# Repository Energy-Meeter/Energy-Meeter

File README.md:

# Energy Meeter

An esp32-powered smart plug and online dashboard.

## Features

- Online dashboard
- WiFi communication
- Capable of analyzing the power consumption of an arbitrary load
- 5A current rating

## Hardware

### Board Revision A

Status: Testing

The current revision of the energy meeter. We just received it from PCBWay, and we're now in the process of assembling and validating it.

#### Schematic

#### Board

#### Stack Up

## Software

### Networking and Dashboard

### Energy Monitor Library

- [HLW8032 energy monitor library](https://github.com/Energy-Meeter/HLW8032)

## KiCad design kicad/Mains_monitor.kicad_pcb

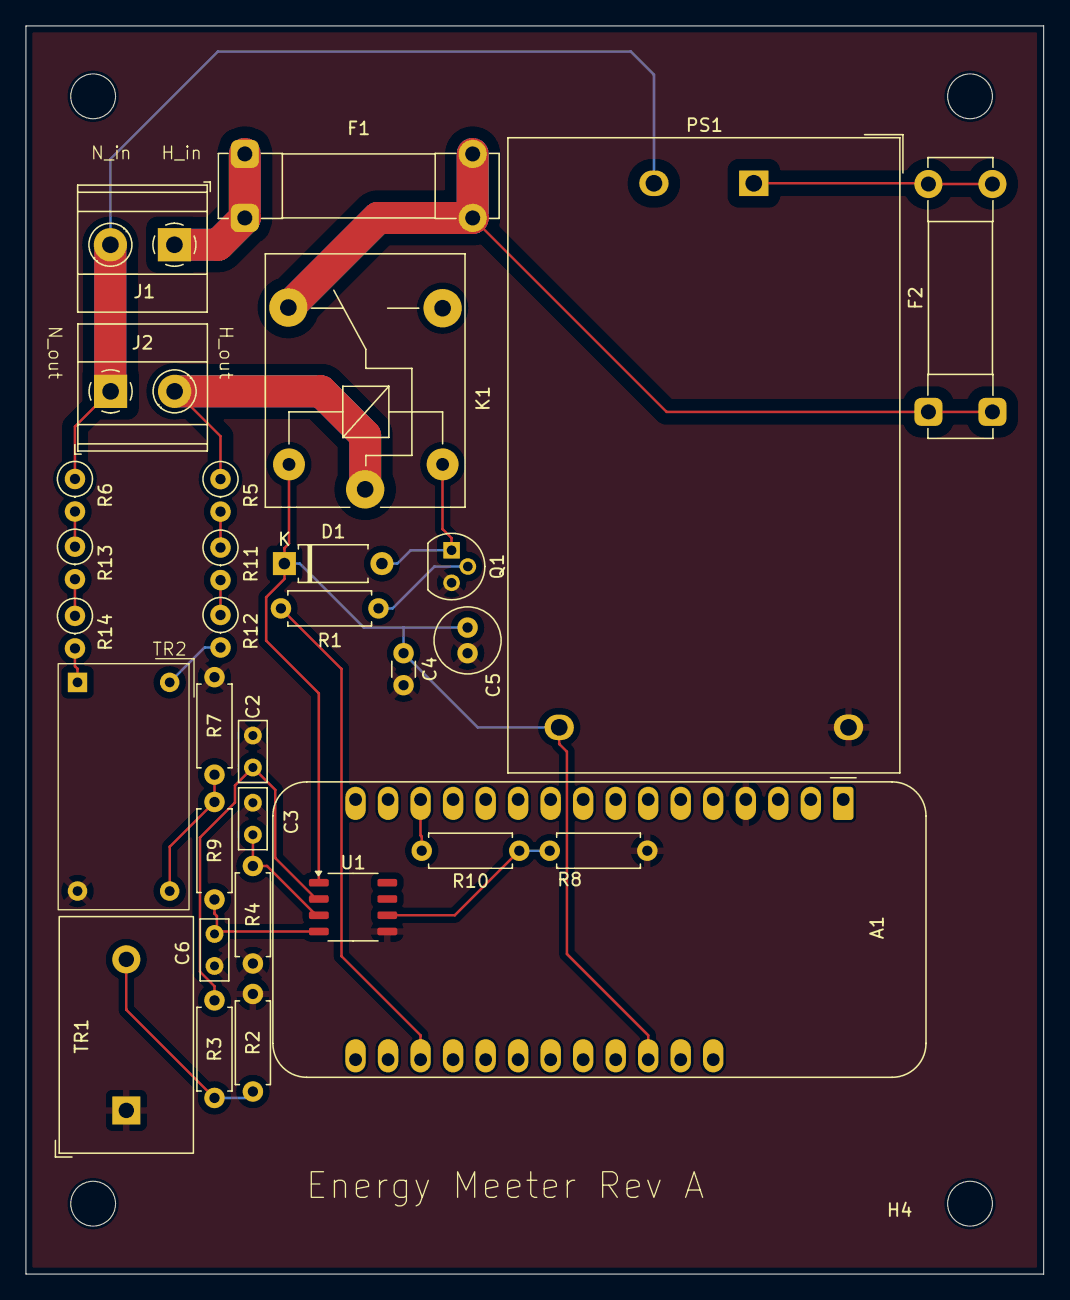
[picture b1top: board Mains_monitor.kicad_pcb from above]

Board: 2 copper layers, 79.5 x 97.5 mm, 35 parts (0 on the bottom side), 23 nets.

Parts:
A1: Adafruit_Feather_HUZZAH32_ESP32; Adafruit_Feather
C2, C3, C6: 33n; C_Rect_L4.6mm_W2.0mm_P2.50mm_MKS02_FKP02
C4: 100n; C_Disc_D3.0mm_W1.6mm_P2.50mm
C5: 10u; C_Radial_D5.0mm_H11.0mm_P2.00mm
D1: D; D_A-405_P7.62mm_Horizontal
F1: 1Ax250V; Fuseholder_Clip-5x20mm_Bel_FC-203-22_Lateral_P17.80x5.00mm_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
F2: 100mAx250V; Fuseholder_Clip-5x20mm_Bel_FC-203-22_Lateral_P17.80x5.00mm_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
H1, H2, H3, H4: MountingHole; MountingHole_3.5mm
J1, J2: Screw_Terminal_01x02; TerminalBlock_Phoenix_MKDS-1,5-2_1x02_P5.00mm_Horizontal
K1: SANYOU_SRD_Form_C; Relay_SPDT_SANYOU_SRD_Series_Form_C
PS1: HLK-10M05; Converter_ACDC_Hi-Link_HLK-10Mxx
Q1: Q_NPN_CBE; TO-92
R1: TBD; R_Axial_DIN0207_L6.3mm_D2.5mm_P7.62mm_Horizontal
R2: 49.9 (1%); R_Axial_DIN0207_L6.3mm_D2.5mm_P7.62mm_Horizontal
R3, R4, R9: 1k; R_Axial_DIN0207_L6.3mm_D2.5mm_P7.62mm_Horizontal
R5, R6, R11, R12, R13, R14: 10K; R_Axial_DIN0207_L6.3mm_D2.5mm_P2.54mm_Vertical
R7: 75 (1%); R_Axial_DIN0207_L6.3mm_D2.5mm_P7.62mm_Horizontal
R8: 5k1; R_Axial_DIN0207_L6.3mm_D2.5mm_P7.62mm_Horizontal
R10: 10k; R_Axial_DIN0207_L6.3mm_D2.5mm_P7.62mm_Horizontal
TR1: ZMCT103C; Transformer_Zeming_ZMCT103C
TR2: ZMPT107; ZMPT107-1
U1: HLW8032; SSOP-8_3.9x5.05mm_P1.27mm

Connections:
+5V: A1.26 (USB), C4.1, C5.2, D1.1 (K), K1.5, PS1.4 (+Vout), U1.1 (VDD)
/DATA_HV: R8.1, R10.1, U1.6 (TX)
/DATA_LV: A1.14 (RX/IO16), R10.2
/RLY_CTRL: A1.19 (A6/IO14), R1.1
AC_H: F1.2, F2.1, K1.4
AC_N: J1.2, J2.1, PS1.2 (AC/N), R6.1
GND: A1.4 (GND), C2.2, C3.1, C4.2, C5.1, C6.2, PS1.3 (-Vout), Q1.3 (E), R2.2, R4.1, R7.1, R8.2, TR1.1, TR2.3, U1.5 (GND)
IN: C3.2, R4.2, U1.3 (IN)
IP: C2.1, R3.2, U1.2 (IP)
unnamed: D1.2 (A), K1.2, Q1.1 (C)
unnamed: F1.1, J1.1
unnamed: F2.2, PS1.1 (AC/L)
unnamed: Q1.2 (B), R1.2
unnamed: R2.1, R3.1, TR1.2
unnamed: R7.2, R9.1, TR2.4
unnamed: R5.2, R11.1
unnamed: R11.2, R12.1
unnamed: R12.2, TR2.2
unnamed: R6.2, R13.1
unnamed: R13.2, R14.1
unnamed: R14.2, TR2.1
RELAY_OUT: J2.2, K1.1, R5.1
VP: C6.1, R9.2, U1.4 (VP)

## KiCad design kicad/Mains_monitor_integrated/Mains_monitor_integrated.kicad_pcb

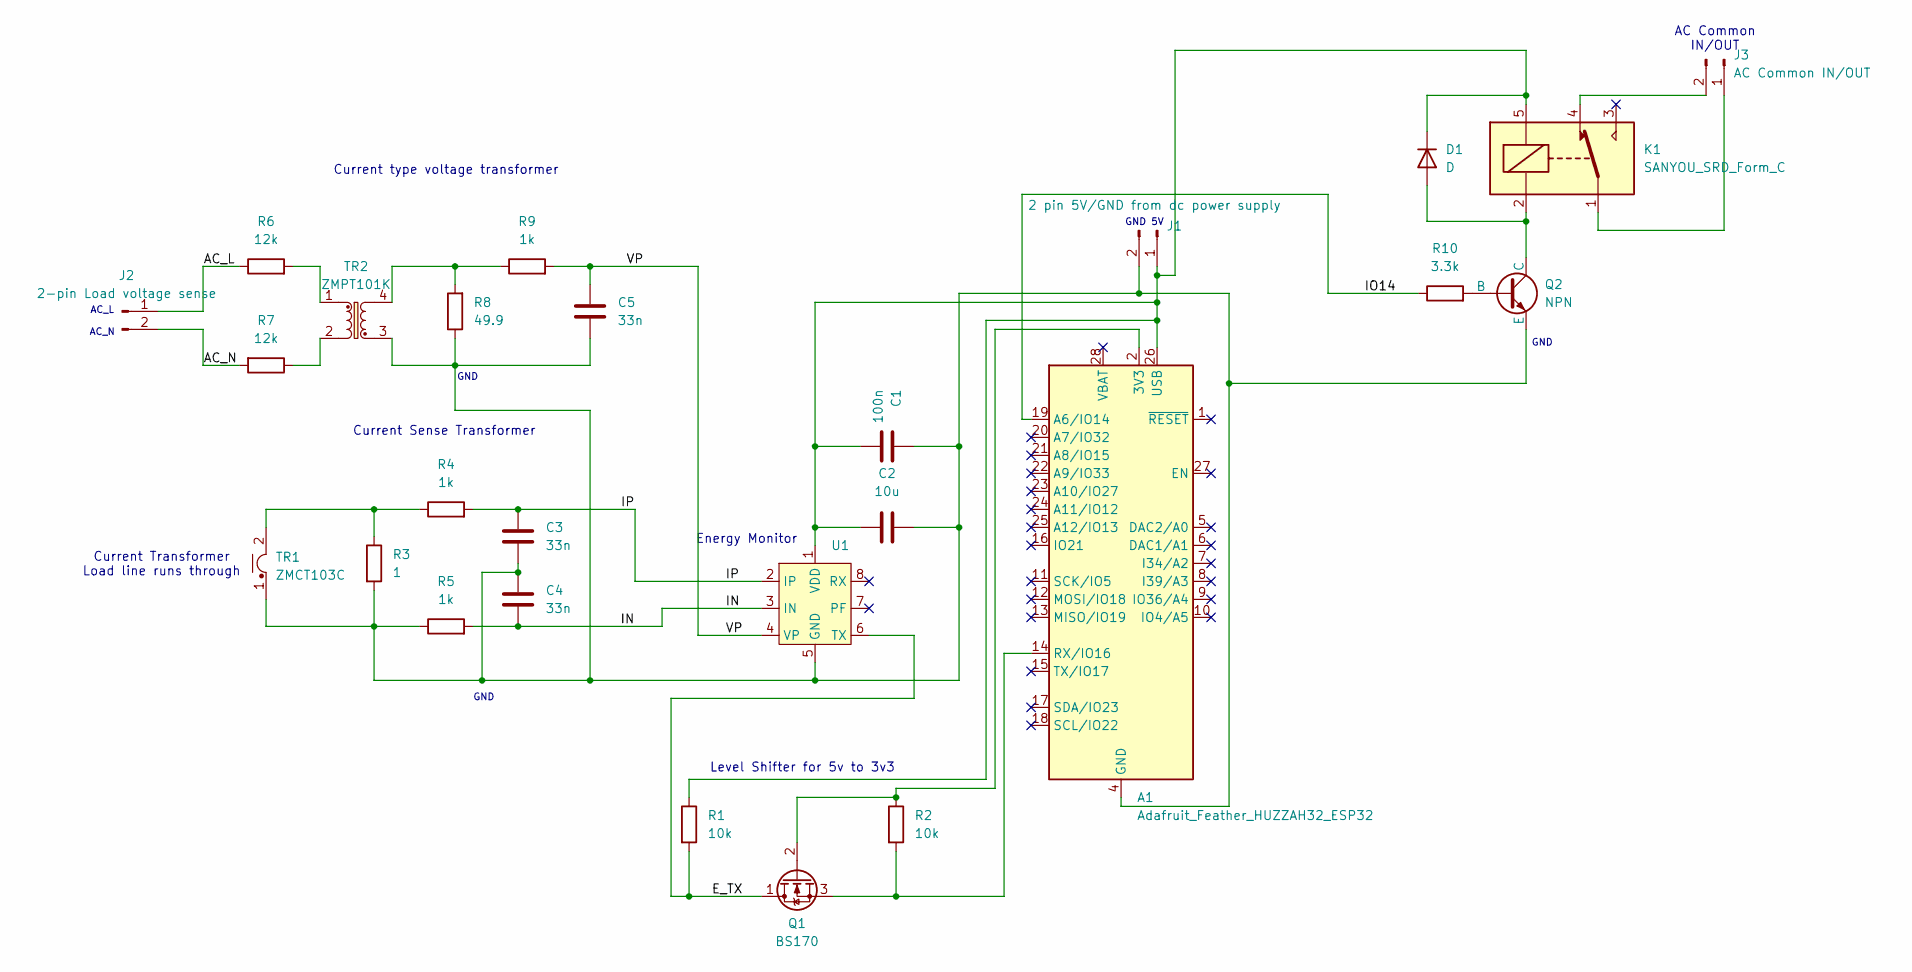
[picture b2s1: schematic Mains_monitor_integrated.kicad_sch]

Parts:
A1: Adafruit_Feather_HUZZAH32_ESP32; Adafruit_Feather
C1: 100n; C_0805_2012Metric_Pad1.18x1.45mm_HandSolder
C2: 10u; C_0805_2012Metric_Pad1.18x1.45mm_HandSolder
C3, C4, C5: 33n; C_0805_2012Metric_Pad1.18x1.45mm_HandSolder
D1: D; D_5W_P10.16mm_Horizontal
J1: 2 pin 5V/GND from dc power supply; PinSocket_1x02_P2.54mm_Vertical
J2: 2-pin Load voltage sense; PinHeader_1x02_P2.54mm_Vertical
J3: AC Common IN/OUT; PinHeader_1x02_P2.54mm_Vertical
K1: SANYOU_SRD_Form_C; Relay_SPDT_SANYOU_SRD_Series_Form_C
Q1: BS170; TO-92_Inline
Q2: NPN; TO-92_Inline
R1, R2: 10k; R_Axial_DIN0414_L11.9mm_D4.5mm_P5.08mm_Vertical
R3: 1; R_Axial_DIN0414_L11.9mm_D4.5mm_P5.08mm_Vertical
R4, R5, R9: 1k; R_Axial_DIN0414_L11.9mm_D4.5mm_P5.08mm_Vertical
R6, R7: 12k; R_Axial_DIN0414_L11.9mm_D4.5mm_P5.08mm_Vertical
R8: 49.9; R_Axial_DIN0414_L11.9mm_D4.5mm_P5.08mm_Vertical
R10: 3.3k; R_Axial_DIN0414_L11.9mm_D4.5mm_P5.08mm_Vertical
TR1: ZMCT103C; Transformer_Zeming_ZMCT103C
TR2: ZMPT101K; Transformer_Zeming_ZMPT101K
U1: HLW8032; SSOP-8_3.9x5.05mm_P1.27mm

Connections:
/AC_L: J2.1, R6.1
/AC_N: J2.2, R7.2
/E_TX: Q1.1 (D), R1.2, U1.6 (TX)
/IN: C4.2, R5.2, U1.3 (IN)
/IO14: A1.19 (A6/IO14), R10.1
/IP: C3.1, R4.2, U1.2 (IP)
/VP: C5.1, R9.2, U1.4 (VP)
unnamed: A1.2 (3V3), Q1.2 (G), R2.1
unnamed: A1.4 (GND), C1.1, C2.1, C3.2, C4.1, C5.2, J1.2, Q2.3 (E), R3.2, R5.1, R8.1, TR1.1, TR2.3, U1.5 (GND)
unnamed: A1.14 (RX/IO16), Q1.3 (S), R2.2
unnamed: A1.26 (USB), C1.2, C2.2, D1.1 (K), J1.1, K1.5, R1.1, U1.1 (VDD)
unnamed: D1.2 (A), K1.2, Q2.1 (C)
unnamed: J3.1, K1.1
unnamed: J3.2, K1.4
unnamed: Q2.2 (B), R10.2
unnamed: R3.1, R4.1, TR1.2
unnamed: R6.2, TR2.1
unnamed: R7.1, TR2.2
unnamed: R8.2, R9.1, TR2.4

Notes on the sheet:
GND
AC_L AC_N
Level Shifter for 5v to 3v3
AC Common IN/OUT
Current Sense Transformer
GND 5V
Current type voltage transformer
Energy Monitor
Current Transformer Load line runs through

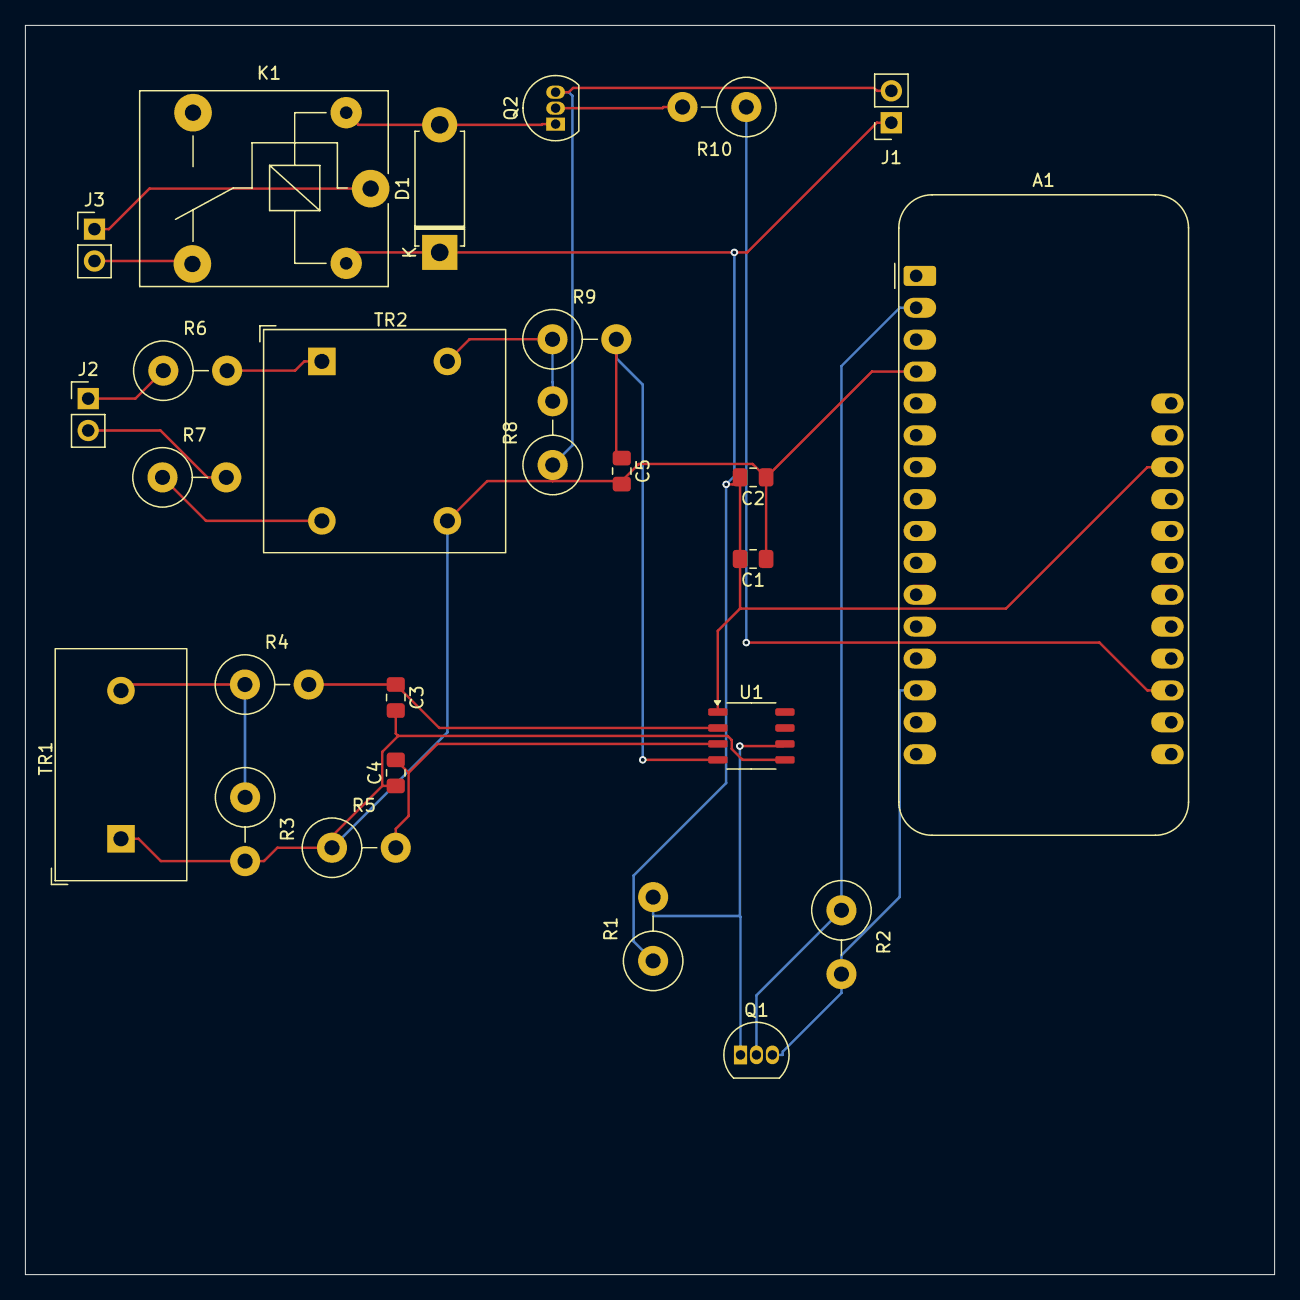
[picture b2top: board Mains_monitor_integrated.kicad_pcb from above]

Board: 2 copper layers, 99.5 x 99.5 mm, 26 parts (0 on the bottom side), 19 nets.

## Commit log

2025-01-01 Init commit
2025-01-01 Create LICENSE
2025-01-01 Design power supply circuit
2025-01-01 Add To Do list
2025-01-17 Add rev0 schematic
2025-01-17 Add pdf of rev0 schematic
2025-01-19 Add git ignore for KiCad Projectt
2025-01-19 Consolidate schematic to a single sheet
2025-01-24 created new schematic to integrate all components into a fully connected final version
2025-01-24 completed rough schematic and built first prototype pcb
2025-01-29 Hello World
2025-01-31 Improve sch clarity
2025-02-03 added footprints for all components, started PCB layout
2025-02-03 added mounting holes and ground layers
2025-02-04 PCB layout updated, traces and base fill added, still need to make space for mounting holes
2025-02-05 added net class for 120V and mounting holes
2025-02-05 backup files
2025-02-06 Update footprints and git ignore
2025-02-06 Get footprint from main
2025-02-06 Added in the correct footprints
2025-02-06 Updated PCB layout with new components, decreased board size
2025-02-06 added updated screw terminal footprints
2025-02-07 Clear ERC, and change Q1
2025-02-07 Clear DRC
2025-02-07 Plot gerbers/drill
2025-02-07 Premptively update gitignore for platform.io
2025-02-07 Add datasheets and supporting documentation for revA
2025-02-07 Add png schematic to add to README
2025-02-07 updated electrical spacing
2025-02-07 added power supply fuse, increased high current trace size, Ready to order
2025-02-07 Added 'Energy Meeter Rev A' to silkscreen
2025-02-13 Add pictures of unpopulated PCB
2025-02-26 update files
